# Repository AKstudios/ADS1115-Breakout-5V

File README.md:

# ADS1115 Breakout 5V
This is a modified version of the ADS1115 breakout board by Adafruit. It takes analog inputs between 0-5V, but the I2C interface is at 3.3V with the addition of logic level shifting circuitry to interface with 3.3V MCUs. All passive components are 0402 parts to fit everything on the board.

The board takes in raw power (2-16V) through the PWR pin and supplies a steady 5V to all components (MCP1703 LDO Vreg). The board has an input header for 3.3V supply for the level shifting circuit.

ALRT pin is not broken out, but still pulled up to 5V on the board.

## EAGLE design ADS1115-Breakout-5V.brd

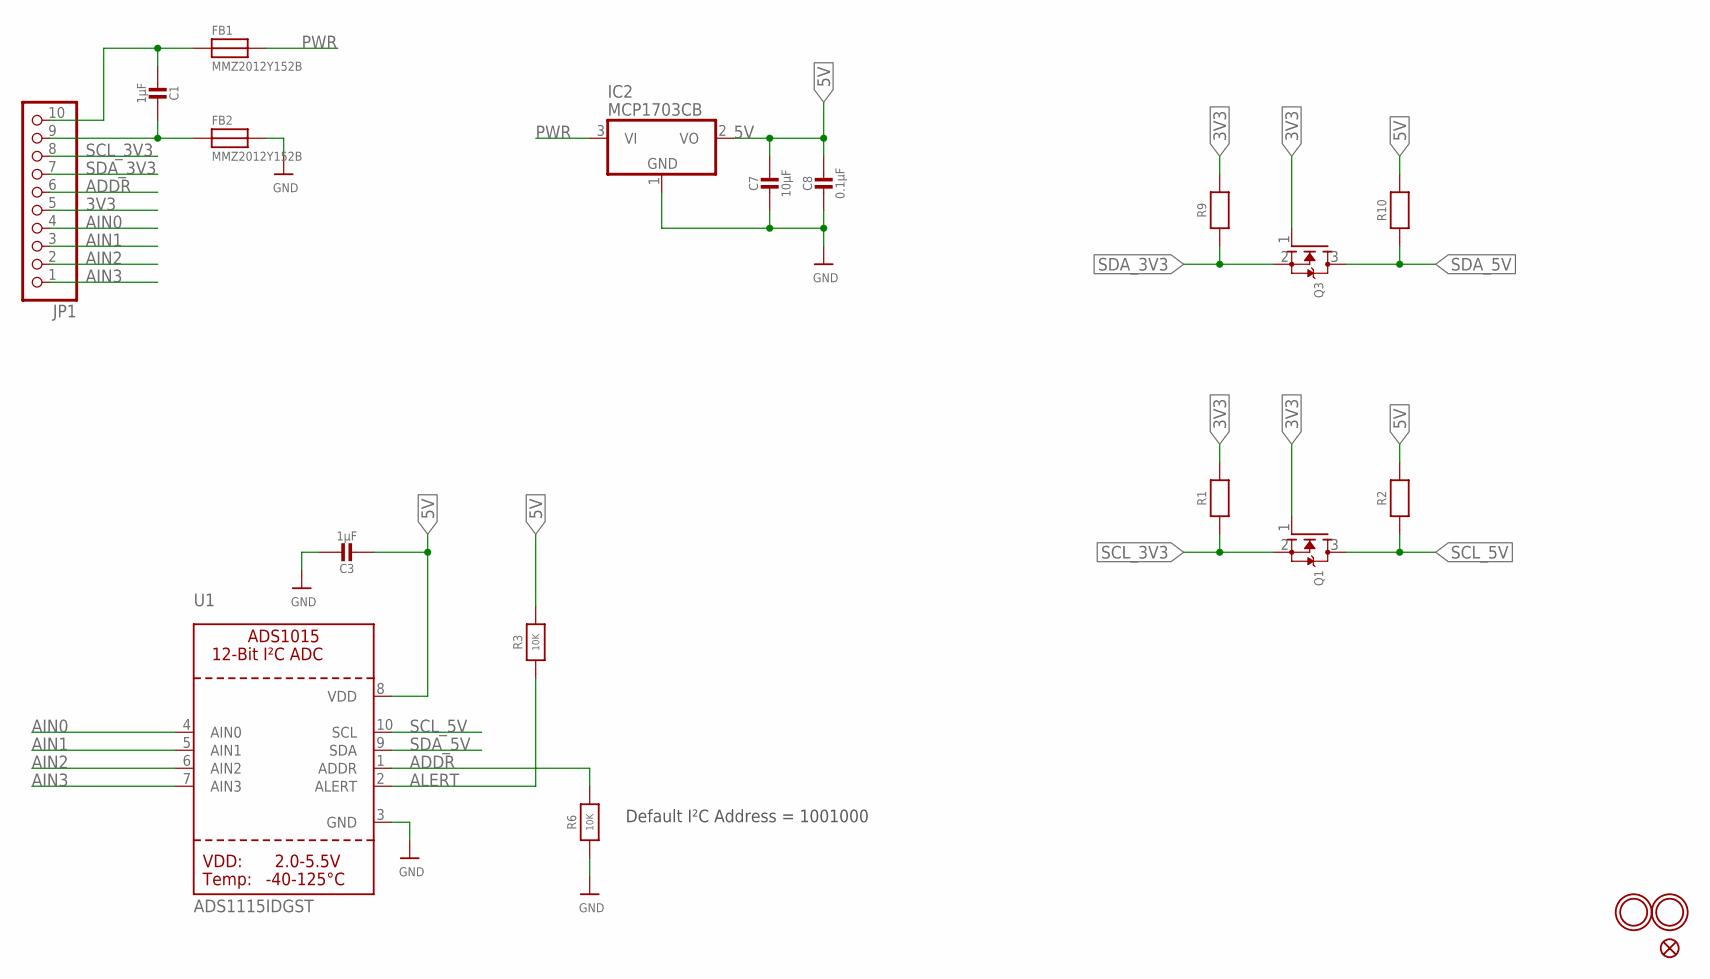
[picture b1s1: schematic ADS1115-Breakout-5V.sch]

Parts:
C1, C3: 1µF; _0402MP
C7: 10µF; _0402MP
C8: 0.1µF; _0402MP
FB1, FB2: MMZ2012Y152B; 0805
FID1: FIDUCIAL""; FIDUCIAL_1MM
IC2: MCP1703CB; SOT23
JP1: HEADER-1X1070MIL; 1X10_ROUND70
Q1, Q3: MOSFET-NREFLOW; SOT23
R1, R2, R9, R10: RESISTOR_0402MP; _0402MP
R3, R6: 10K; _0402MP
U1: ADS1115IDGST; MSOP10
U$13, U$14: MOUNTINGHOLE2.5; MOUNTINGHOLE_2.5_PLATED

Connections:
3V3: JP1.5, Q1.1 (G), Q3.1 (G), R1.2, R9.2
5V: C3.2, C7.1, C8.1, IC2.2 (VO), R2.2, R3.2, R10.2, U1.8 (VDD)
ADDR: JP1.6, R6.2, U1.1 (ADDR)
AIN0: JP1.4, U1.4 (AIN0)
AIN1: JP1.3, U1.5 (AIN1)
AIN2: JP1.2, U1.6 (AIN2)
AIN3: JP1.1, U1.7 (AIN3)
ALERT: R3.1, U1.2 (ALERT)
GND: C3.1, C7.2, C8.2, FB2.2, IC2.1 (GND), R6.1, U1.3 (GND)
unnamed: C1.2, FB1.1, JP1.10
unnamed: C1.1, FB2.1, JP1.9
PWR: FB1.2, IC2.3 (VI)
SCL_3V3: JP1.8, Q1.2 (S), R1.1
SCL_5V: Q1.3 (D), R2.1, U1.10 (SCL)
SDA_3V3: JP1.7, Q3.2 (S), R9.1
SDA_5V: Q3.3 (D), R10.1, U1.9 (SDA)

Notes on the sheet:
Default I²C Address = 1001000

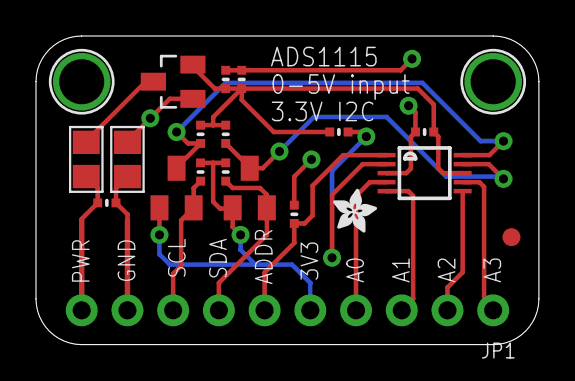
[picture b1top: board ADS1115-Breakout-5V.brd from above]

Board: 2 copper layers, 27.9 x 17.1 mm, 22 parts (1 on the bottom side), 16 nets.

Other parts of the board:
U$15: ADAFRUIT_TEXT_20MM
U$16: ADAFRUIT_2.5MM

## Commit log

2017-04-19 :boom::camel: Added .gitattributes & .gitignore files
2017-04-19 Added EAGLE files
2017-04-19 Some trace & silkscreen adjustments
2017-04-19 Added render
